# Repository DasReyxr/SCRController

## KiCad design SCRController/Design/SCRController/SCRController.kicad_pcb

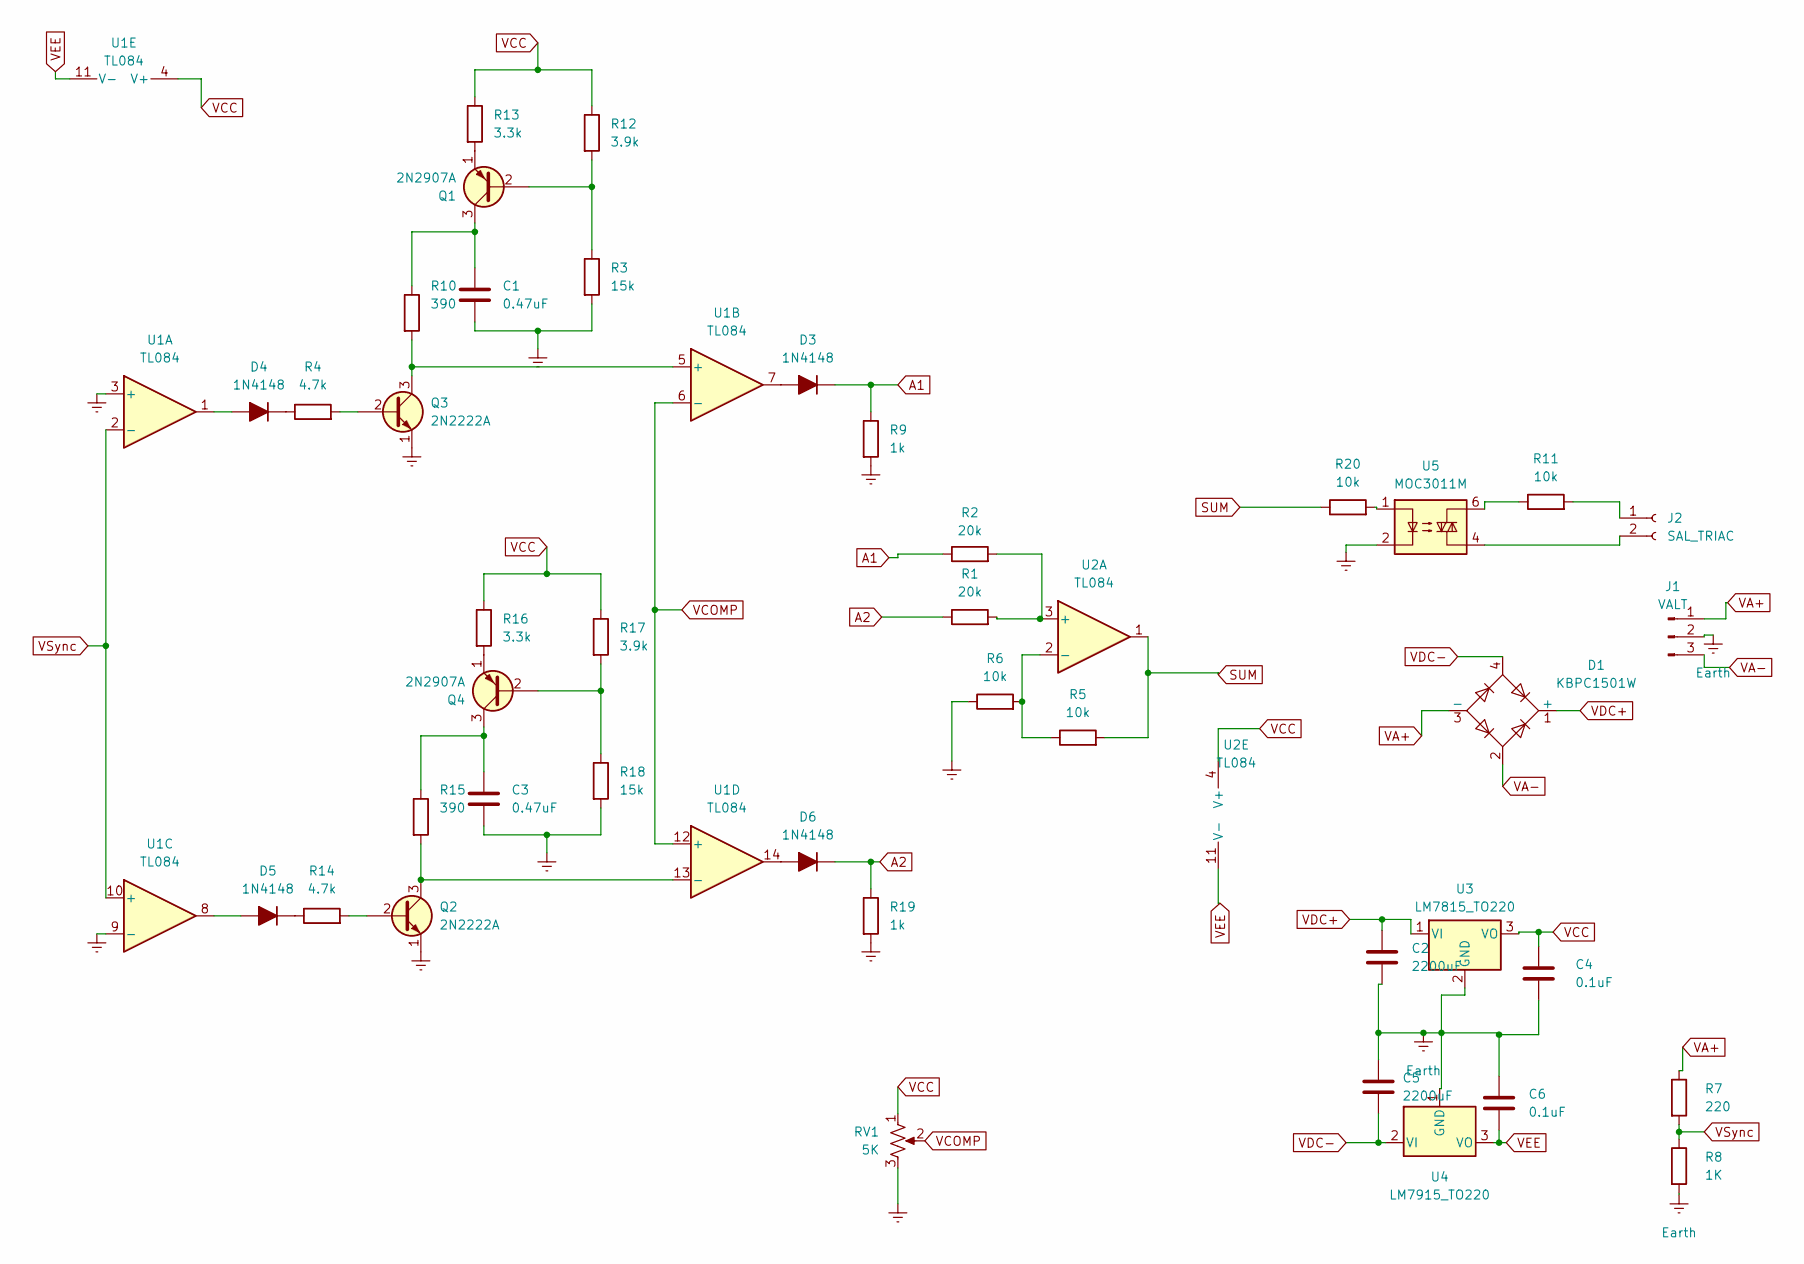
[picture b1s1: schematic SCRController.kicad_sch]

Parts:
C1, C3: 0.47uF; C_Radial_D4.0mm_H5.0mm_P1.50mm
C2, C5: 2200uF; C_Radial_D4.0mm_H5.0mm_P1.50mm
C4, C6: 0.1uF; C_Radial_D4.0mm_H5.0mm_P1.50mm
D1: KBPC1501W; Diode_Bridge_KBP
D3, D4, D5, D6: 1N4148; D_DO-15_P5.08mm_Vertical_AnodeUp
J1: VALT; TerminalBlock_MaiXu_MX126-5.0-03P_1x03_P5.00mm
J2: SAL_TRIAC; TerminalBlock_MaiXu_MX126-5.0-02P_1x02_P5.00mm
Q1, Q4: 2N2907A; TO-92L_Inline
Q2, Q3: 2N2222A; TO-92L_Inline
R1, R2: 20k; R_Axial_DIN0207_L6.3mm_D2.5mm_P7.62mm_Horizontal
R3, R18: 15k; R_Axial_DIN0207_L6.3mm_D2.5mm_P7.62mm_Horizontal
R4, R14: 4.7k; R_Axial_DIN0207_L6.3mm_D2.5mm_P7.62mm_Horizontal
R5, R6, R11, R20: 10k; R_Axial_DIN0207_L6.3mm_D2.5mm_P7.62mm_Horizontal
R7: 220; R_Axial_DIN0207_L6.3mm_D2.5mm_P7.62mm_Horizontal
R8: 1K; R_Axial_DIN0207_L6.3mm_D2.5mm_P7.62mm_Horizontal
R9, R19: 1k; R_Axial_DIN0207_L6.3mm_D2.5mm_P7.62mm_Horizontal
R10, R15: 390; R_Axial_DIN0207_L6.3mm_D2.5mm_P7.62mm_Horizontal
R12, R17: 3.9k; R_Axial_DIN0207_L6.3mm_D2.5mm_P7.62mm_Horizontal
R13, R16: 3.3k; R_Axial_DIN0207_L6.3mm_D2.5mm_P7.62mm_Horizontal
RV1: 5K; Potentiometer_Alps_RK163_Single_Horizontal
U1, U2: TL084; DIP-14_W7.62mm_LongPads
U3: LM7815_TO220; TO-220-3_Vertical
U4: LM7915_TO220; TO-220-3_Vertical
U5: MOC3011M; DIP-6_W7.62mm_LongPads

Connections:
A1: D3.1 (K), R2.1, R9.1
A2: D6.1 (K), R1.1, R19.1
Earth: C1.2, C2.2, C3.2, C4.2, C5.1, C6.1, J1.2, Q2.1 (E), Q3.1 (E), R3.2, R6.1, R8.2, R9.2, R18.2, R19.2, RV1.3, U1.3 (+), U1.9 (-), U3.2 (GND), U4.1 (GND), U5.2
unnamed: D3.2 (A), U1.7
unnamed: D4.2 (A), U1.1
unnamed: D4.1 (K), R4.1
unnamed: D5.2 (A), U1.8
unnamed: D5.1 (K), R14.1
unnamed: D6.2 (A), U1.14
unnamed: J2.1, R11.2
unnamed: J2.2, U5.4
unnamed: Q1.2 (B), R3.1, R12.2
unnamed: C1.1, Q1.3 (C), R10.1
unnamed: Q1.1 (E), R13.2
unnamed: Q2.2 (B), R14.2
unnamed: Q2.3 (C), R15.2, U1.13 (-)
unnamed: Q3.2 (B), R4.2
unnamed: Q3.3 (C), R10.2, U1.5 (+)
unnamed: Q4.2 (B), R17.2, R18.1
unnamed: C3.1, Q4.3 (C), R15.1
unnamed: Q4.1 (E), R16.2
unnamed: R11.1, U5.6
unnamed: R20.2, U5.1
unnamed: R1.2, R2.2, U2.3 (+)
unnamed: R5.1, R6.2, U2.2 (-)
SUM: R5.2, R20.1, U2.1
VA+: D1.3 (-), J1.1, R7.1
VA-: D1.2, J1.3
VCC: C4.1, R12.1, R13.1, R16.1, R17.1, RV1.1, U1.4 (V+), U2.4 (V+), U3.3 (VO)
VCOMP: RV1.2, U1.6 (-), U1.12 (+)
VDC+: C2.1, D1.1 (+), U3.1 (VI)
VDC-: C5.2, D1.4, U4.2 (VI)
VEE: C6.2, U1.11 (V-), U2.11 (V-), U4.3 (VO)
VSync: R7.2, R8.1, U1.2 (-), U1.10 (+)

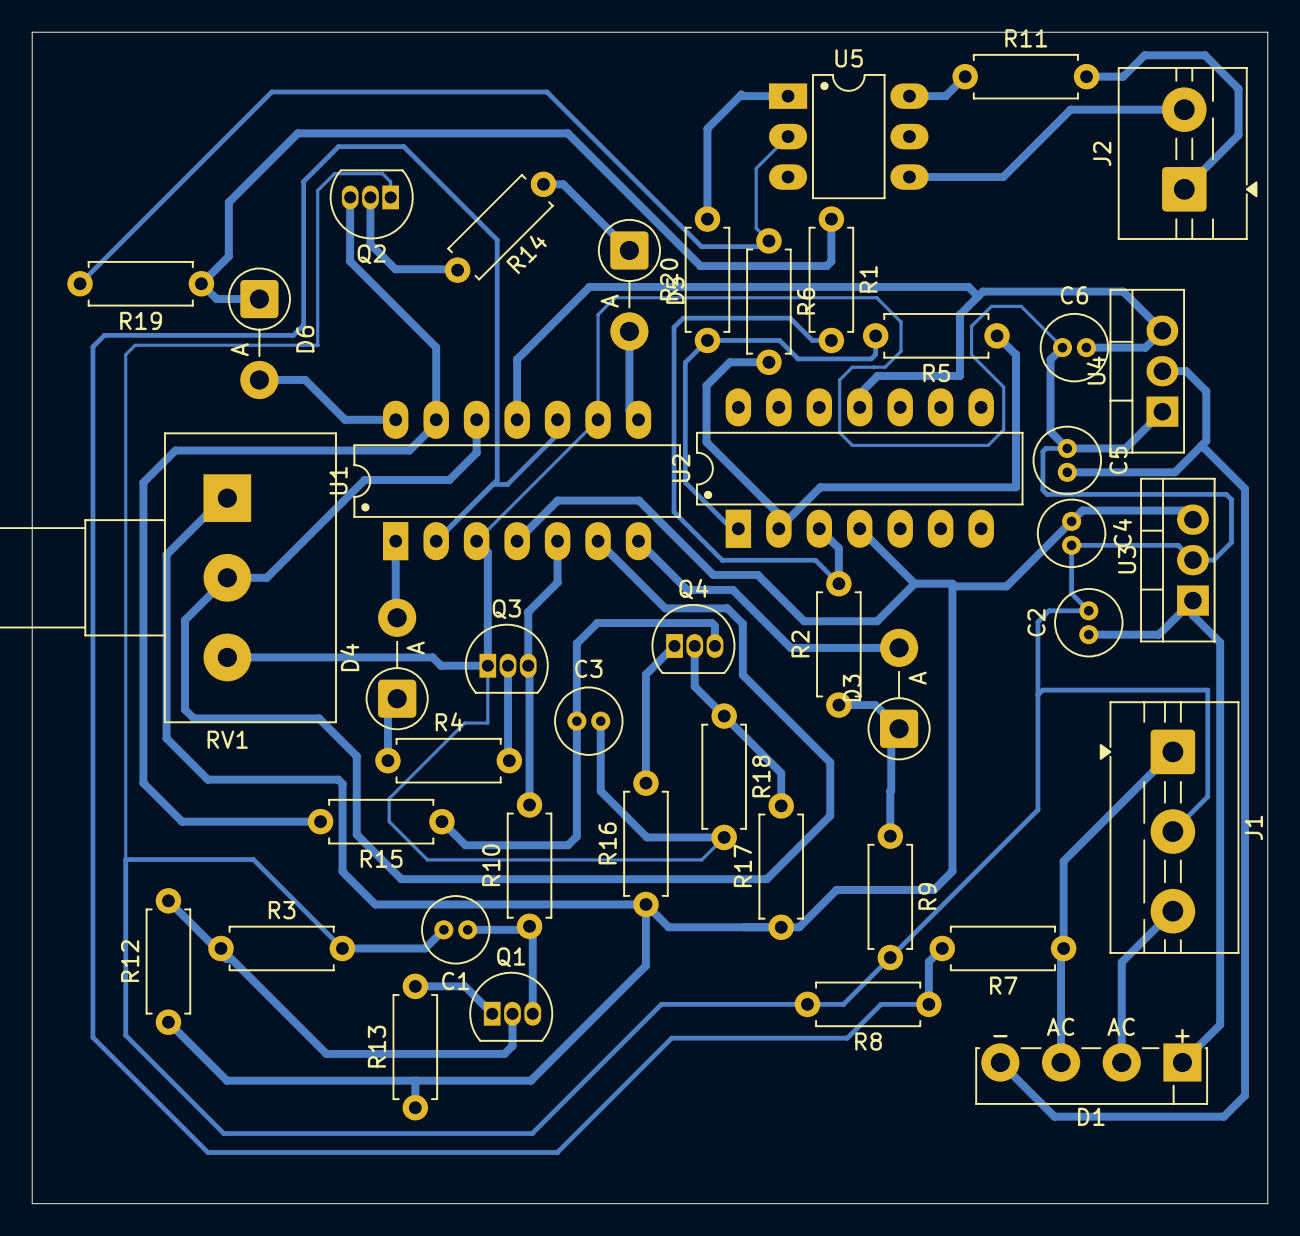
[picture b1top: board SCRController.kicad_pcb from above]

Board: 2 copper layers, 77.6 x 73.5 mm, 43 parts (0 on the bottom side), 34 nets.

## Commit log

2026-02-28 Created Project n Design
2026-03-06 Se agregaron footprints basicas, pero falta etapa 1 y 5
2026-03-10 Added PowerSupply
2026-03-10 Se añadio reguladores, puente de diodos sumador y optoacoplador
2026-03-10 Añadio alimentacion opamps
2026-03-10 Rearranged the files
2026-03-10 Added Sim
2026-03-11 Updated footprints
2026-03-11 Update SCRController design files
2026-03-11 Changed FP
2026-03-11 Placed Footprints and first routed
2026-03-12 Pcb full
2026-03-14 added Sim of PowerSupply
2026-03-17 Correcciones
2026-03-18 rehecho
2026-04-15 Added Designs of Multisim
2026-04-15 Addded Gabi
2026-05-04 4-5-26
2026-05-04 Renamed
2026-05-05 Added maxima file'
